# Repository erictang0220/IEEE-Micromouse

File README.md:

# IEEE Micromouse Project

## Goal
* Design autonomous car that can navigate itself to the middle of the maze

## Software (in C language)
* Implemented PID to control the two motors of the car 
* Implemented the floodfill algorithm to help the car keep track of the path it has travelled and update its distance matrix accordingly

## Hardware
### Mouse PCB
* Incorporated H-bridge, photodiodes, IR sensors, transistors, and capacitors on to the mouse PCB
* Uploaded the code with different hardware configuration to test out PID constants

### IR Breakout Board
* Designed a PCB with three photodiodes and IR sensors in Eagle
* Thickened the tracing to ensure optimal current

## Results
* Download and watch the video [here](https://github.com/erictang0220/IEEE-Micromouse/blob/main/micromouse/good%20no%20aud%202.mov)
* [PCB in design](https://github.com/erictang0220/IEEE-Micromouse/blob/main/micromouse/Eagle%20breakout%20board.png) and the [final product](https://github.com/erictang0220/IEEE-Micromouse/blob/main/micromouse/made%20breakout%20board.png)!

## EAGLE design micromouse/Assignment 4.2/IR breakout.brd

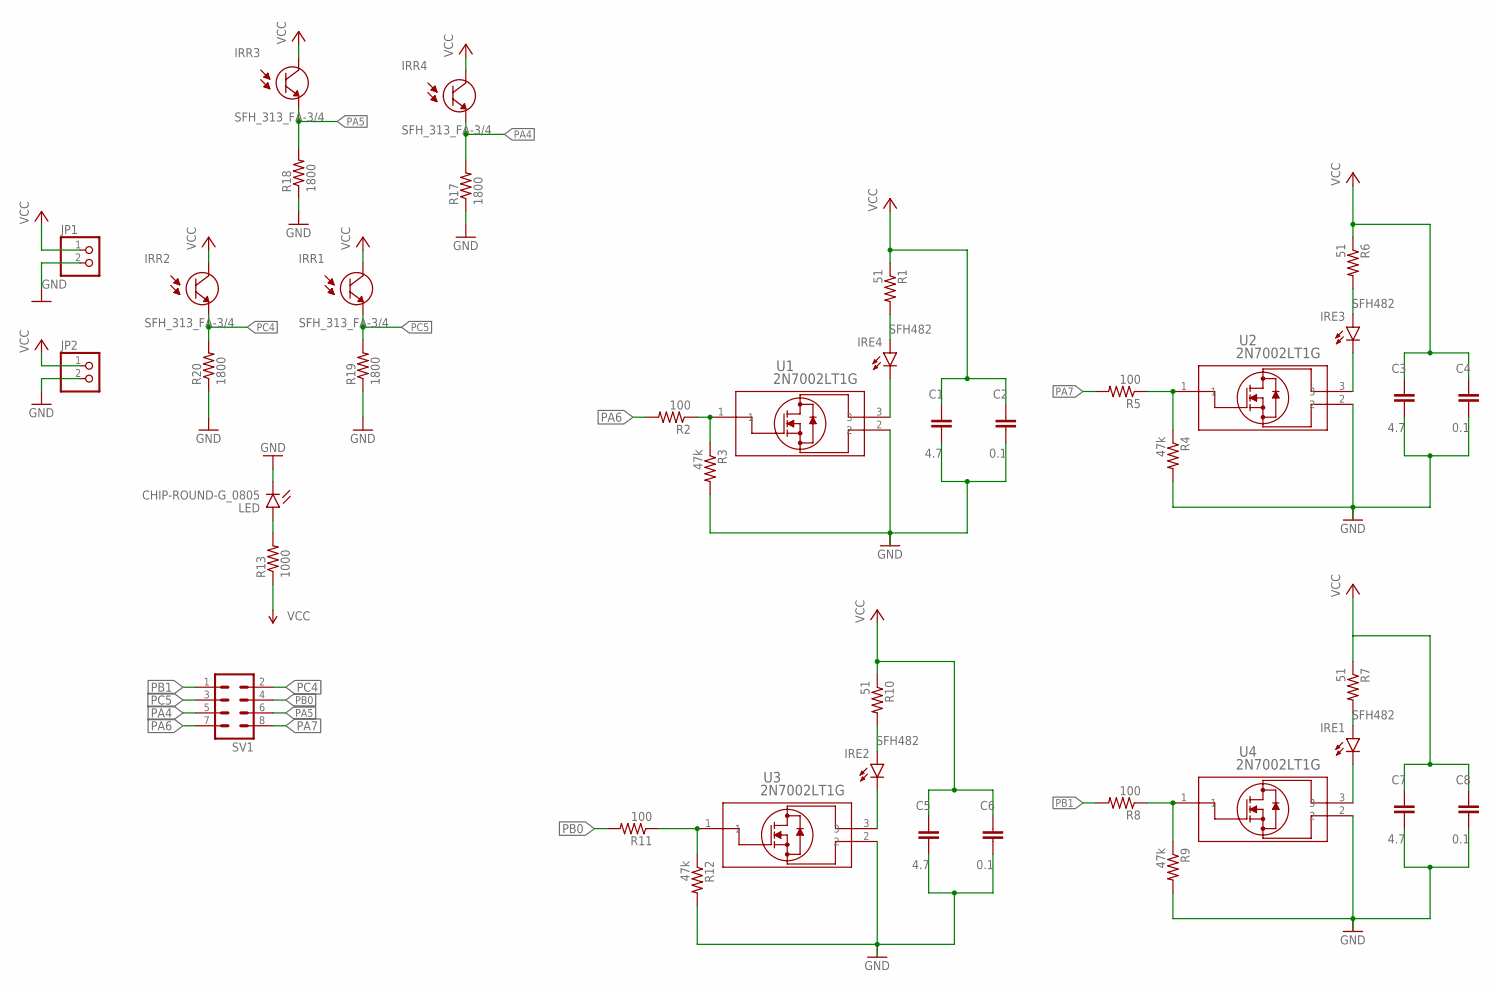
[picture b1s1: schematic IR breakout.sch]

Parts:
C1, C3, C5, C7: 4.7; CAP_0805
C2, C4, C6, C8: 0.1; CAP_0805
IRE1, IRE2, IRE3, IRE4: SFH482
IRR1, IRR2, IRR3, IRR4: SFH_313_FA-3/4; XDCR_SFH_313_FA-3/4
JP1, JP2: PINHD-1X2; 1X02
LED: CHIP-ROUND-G_0805; LEDC2012X105N_RND-G
R1, R6, R7, R10: 51; RES_0805
R2, R5, R8, R11: 100; RES_0805
R3, R4, R9, R12: 47k; RES_0805
R13: 1000; RES_0805
R17, R18, R19, R20: 1800; RES_0805
SV1: MA04-2
U1, U2, U3, U4: 2N7002LT1G; SOT-23_3L_ONS

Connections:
GND: C1.2, C2.2, C3.2, C4.2, C5.2, C6.2, C7.2, C8.2, JP1.2, JP2.2, LED.C, R3.2, R4.2, R9.2, R12.2, R17.1, R18.1, R19.1, R20.1, U1.2, U2.2, U3.2, U4.2
unnamed: IRE3.K (C), U2.3
unnamed: IRE4.K (C), U1.3
unnamed: R2.1, R3.1, U1.1
unnamed: IRE4.A, R1.2
unnamed: IRE2.A, R10.2
unnamed: R11.1, R12.1, U3.1
unnamed: IRE3.A, R6.2
unnamed: LED.A, R13.2
unnamed: R4.1, R5.1, U2.1
unnamed: IRE2.K (C), U3.3
unnamed: IRE1.K (C), U4.3
unnamed: IRE1.A, R7.2
unnamed: R8.1, R9.1, U4.1
PA4: IRR4.1 (E), R17.2, SV1.5
PA5: IRR3.1 (E), R18.2, SV1.6
PA6: R2.2, SV1.7
PA7: R5.2, SV1.8
PB0: R11.2, SV1.4
PB1: R8.2, SV1.1
PC4: IRR2.1 (E), R20.2, SV1.2
PC5: IRR1.1 (E), R19.2, SV1.3
VCC: C1.1, C2.1, C3.1, C4.1, C5.1, C6.1, C7.1, C8.1, IRR1.2 (C), IRR2.2 (C), IRR3.2 (C), IRR4.2 (C), JP1.1, JP2.1, R1.1, R6.1, R7.1, R10.1, R13.1

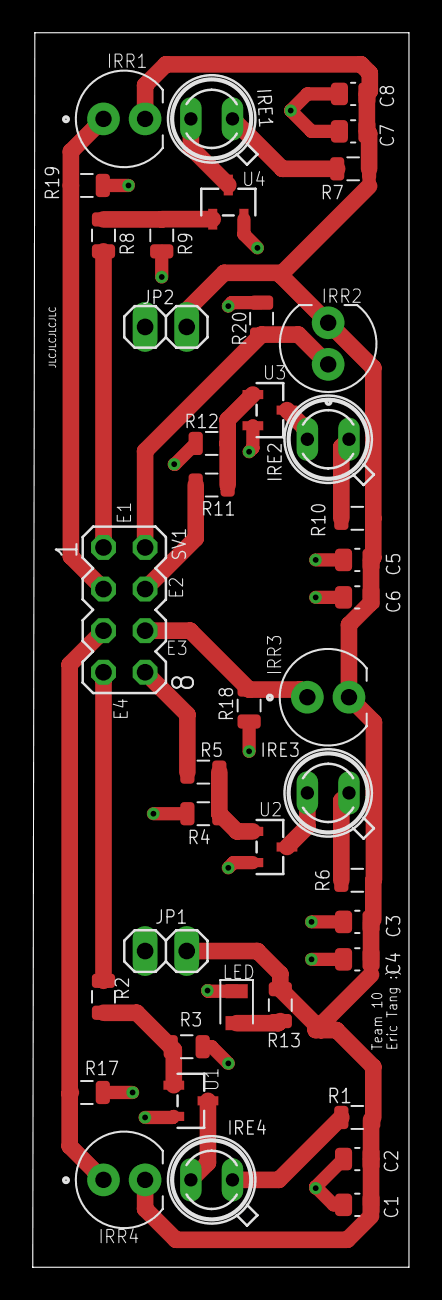
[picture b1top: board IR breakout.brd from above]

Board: 2 copper layers, 23.0 x 75.4 mm, 41 parts (0 on the bottom side), 23 nets.

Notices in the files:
parts and their libraries:
COPYRIGHT: Copyright (C) 2018 Accelerated Designs. All rights reserved
SparkFun-PowerSymbols: Licensing: Creative Commons ShareAlike 4.0 International - https://creativecommons.org/licenses/by-sa/4.0
